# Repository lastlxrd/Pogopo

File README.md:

# Pogopo

*Both Pogopo and PogopoOS are still in the early stages of development.*

[@lastlxrd](https://github.com/lastlxrd) 2026

## Getting Started

Pogopo is still under active development. More complete documentation will be added as the hardware and software mature.

[Documentation](https://lastlxrd.github.io/Pogopo/)
[FAQ](https://lastlxrd.github.io/Pogopo/faq/)

## Project Summary

Pogopo is a custom hand-built handheld console based on the ESP32-S3. It combines a low-power monochrome display, physical controls, audio, motion sensing, removable storage, haptic feedback, and custom power management in one compact device.

The goal is to create a standalone handheld capable of running native applications, utilities, emulators, and custom games through a simple graphical interface. The current device is a working development prototype, with both its hardware and software continuing to evolve.

## Hardware

- ESP32-S3 with 16 MB flash and 8 MB PSRAM
- Sharp LS027B7DH01 400 × 240 Memory LCD
- BMI270 motion sensor
- MAX98357A I2S audio amplifier
- microSD card over 4-bit SDMMC
- TCA9555 GPIO and button expander
- D-pad, A, B, Menu, Start, and Power controls
- Vibration motor
- Rechargeable battery
- Onboard charging and power management
- Custom PCB and 3D-printed enclosure

## PogopoOS

PogopoOS is the custom operating system and application platform developed specifically for the Pogopo console.

- ESP-IDF-based firmware
- Graphical launcher and application framework
- Reusable display, input, audio, storage, and sensor drivers
- Native I2S audio and WAV playback
- Motion sensing and visualization tools
- microSD file access
- Persistent settings
- Power quick menu and clean LCD shutdown
- Haptic feedback
- Native Game Boy emulation
- Full-speed Game Boy CPU execution
- Approximately 30 FPS LCD presentation
- Four-shade ordered dithering
- Fixed-rate Game Boy audio
- ROM loading from microSD
- Experimental PDX and Lua game runtime

Game ROMs and third-party game files are not included in this repository.

## Development

Pogopo and PogopoOS are developed through small tested milestones. Commit messages contain short summaries of individual changes, while longer technical notes are stored in [`docs/history/`](docs/history/).

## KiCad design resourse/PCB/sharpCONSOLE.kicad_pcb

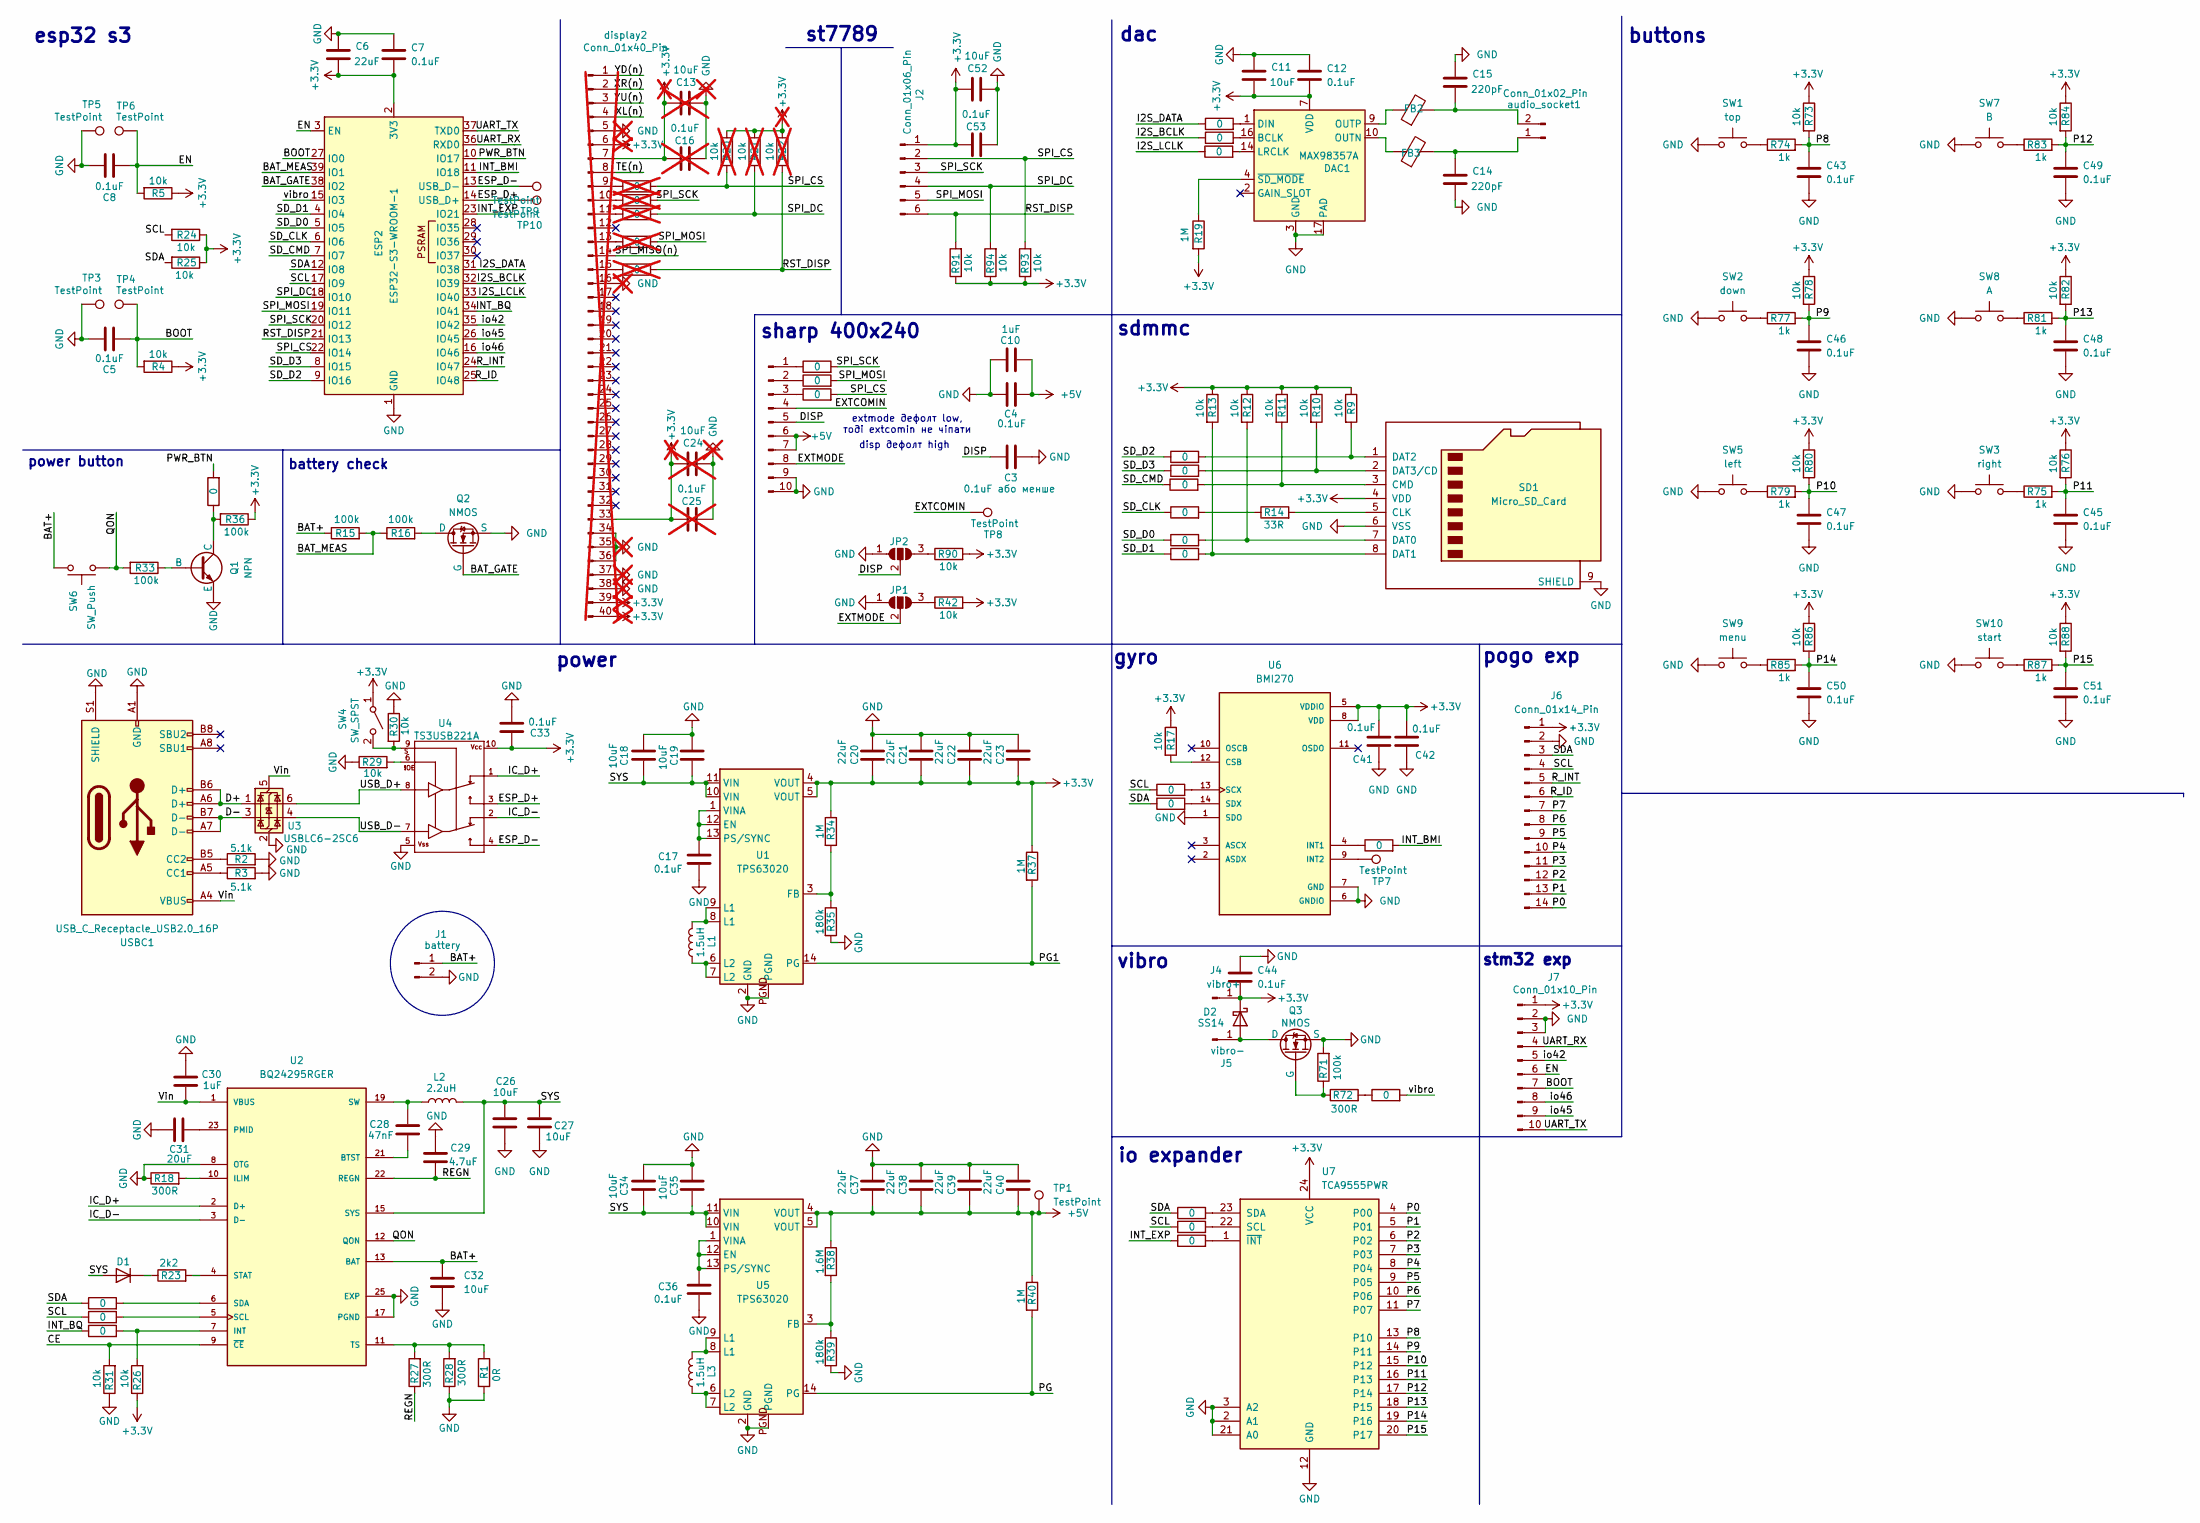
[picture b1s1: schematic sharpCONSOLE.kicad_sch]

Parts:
C3: 0.1uF або менше; C_0805_2012Metric
C4, C5, C7, C8, C12, C17, C33, C36, C41, C42, C43, C44, C45, C46, C47, C48, C49, C50, C51, C53: 0.1uF; C_0805_2012Metric
C6, C20, C21, C22, C23, C37, C38, C39, C40: 22uF; C_0805_2012Metric
C10, C30: 1uF; C_0805_2012Metric
C11, C18, C19, C26, C27, C32, C34, C35, C52: 10uF; C_0805_2012Metric
C13, C24: 10uF; C_0805_2012Metric; not fitted
C14, C15: 220pF; C_0805_2012Metric
C16, C25: 0.1uF; C_0805_2012Metric; not fitted
C28: 47nF; C_0805_2012Metric
C29: 4.7uF; C_0805_2012Metric
C31: 20uF; C_0805_2012Metric
D1: D; LED_0805_2012Metric
D2: SS14; D_SMA
DAC1: MAX98357A; TQFN-16-1EP_3x3mm_P0.5mm_EP1.23x1.23mm
ESP2: ESP32-S3-WROOM-1
FB2, FB3: 600; R_0805_2012Metric
J1: battery; PinHeader_1x02_P2.54mm_Vertical
J2: Conn_01x06_Pin; pad_6pin
J4: vibro+; TestPoint_Pad_1.5x1.5mm
J5: vibro-; TestPoint_Pad_1.5x1.5mm
J6: Conn_01x14_Pin; pads rp2040
J7: Conn_01x10_Pin; pad_10pin
J9: Conn_01x10_Pin; TE_1-1734839-0_1x10-1MP_P0.5mm_Horizontal
JP1, JP2: SolderJumper_3_Open; SolderJumper-3_P1.3mm_Open_RoundedPad1.0x1.5mm
L1, L3: 1.5uH; L_Chilisin_BMRA00050530
L2: 2.2uH; L_Chilisin_BMRA00050530
Q1: NPN; SOT-23-3
Q2, Q3: NMOS; SOT-23
R1: 0R; R_0805_2012Metric
R2, R3: 5.1k; R_0805_2012Metric
R4, R5, R9, R10, R11, R12, R13, R17, R24, R25, R26, R29, R30, R31, R42, R73, R76, R78, R80, R82, R84, R86, R88, R90, R91, R93, R94: 10k; R_0805_2012Metric
R14: 33R; R_0805_2012Metric
R15, R16, R33, R36, R71: 100k; R_0805_2012Metric
R18, R27, R28, R72: 300R; R_0805_2012Metric
R19, R34, R37, R40: 1M; R_0805_2012Metric
R20, R21, R22: 10k; R_0805_2012Metric; not fitted
R23: 2k2; R_0805_2012Metric
R35, R39: 180k; R_0805_2012Metric
R38: 1.6M; R_0805_2012Metric
R43, R44, R45, R46, R47, R48, R52, R53, R54, R55, R56, R57, R58, R59, R60, R61, R62, R63, R64, R70, R96, R97, R98: 0; R_0402_1005Metric
R65, R66, R67, R68, R69: 0; R_0402_1005Metric; not fitted
R74, R75, R77, R79, R81, R83, R85, R87: 1k; R_0805_2012Metric
SD1: Micro_SD_Card; microSD_HC_Hirose_DM3AT-SF-PEJM5
SW1: top; SW_Dome_10mm
SW2: down; SW_Dome_10mm
SW3: right; SW_Dome_10mm
SW4: SW_SPST; SW_DIP_SPSTx01_Slide_Copal_CVS-01xB_W5.9mm_P1mm
SW5: left; SW_Dome_10mm
SW6: SW_Push; SW_SPST_B3U-3000P
SW7: B; SW_Dome_10mm
SW8: A; SW_Dome_10mm
SW9: menu; SW_Dome_10mm
SW10: start; SW_Dome_10mm
TP1: TestPoint; TestPoint_Pad_1.5x1.5mm
TP3, TP4, TP5, TP6, TP9, TP10: TestPoint; TestPoint_Pad_D1.0mm
TP7, TP8: TestPoint; TestPoint_Pad_1.0x1.0mm
U1, U5: TPS63020
U2: BQ24295RGER; IC_BQ24295RGER; PARTREV B
U3: USBLC6-2SC6; SOT-23-6
U4: TS3USB221A; QFN-10-RSE
U6: BMI270; XDCR_BMI270
U7: TCA9555PWR; TSSOP-24_4.4x7.8mm_P0.65mm
USBC1: USB_C_Receptacle_USB2.0_16P; USB_C_Receptacle_GCT_USB4110
audio_socket1: Conn_01x02_Pin; PinHeader_1x02_P2.00mm_Vertical
display2: Conn_01x40_Pin; Hirose_FH12-40S-0.5SH_1x40-1MP_P0.50mm_Horizontal; not fitted

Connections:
+3.3V: C6.2, C7.2, C11.2, C12.2, C13.2, C16.2, C20.1, C21.1, C22.1, C23.1, C24.2, C25.2, C33.2, C41.2, C42.2, C44.2, C52.2, C53.2, D2.1 (K), DAC1.7 (VDD), DAC1.8 (VDD), ESP2.2 (3V3), J2.1, J4.1, J6.1, J7.1, R4.1, R5.1, R9.1, R10.1, R11.1, R12.1, R13.1, R17.1, R19.2, R20.1, R21.1, R22.1, R24.1, R25.1, R26.1, R34.1, R36.1, R37.1, R42.2, R73.1, R76.1, R78.1, R80.1, R82.1, R84.1, R86.1, R88.1, R90.2, R91.1, R93.1, R94.1, SD1.4 (VDD), SW4.1 (A), U1.4 (VOUT), U1.5 (VOUT), U4.10, U6.5 (VDDIO), U6.8 (VDD), U7.24 (VCC), display2.6, display2.7, display2.33, display2.39, display2.40
+5V: C4.2, C10.2, C37.1, C38.1, C39.1, C40.1, J9.6, J9.7, R38.1, R40.1, TP1.1, U5.4 (VOUT), U5.5 (VOUT)
/BAT+: C32.1, J1.1, R15.1, SW6.2, U2.13 (BAT), U2.14 (BAT)
/BAT_GATE: ESP2.38 (IO2), Q2.2 (G)
/BAT_MEAS: ESP2.39 (IO1), R15.2, R16.1
/BOOT: C5.1, ESP2.27 (IO0), J7.7, R4.2, TP4.1
/CE: R31.2, U2.9 (~CE)
/D+: U3.1 (I/O1), USBC1.A6 (D+), USBC1.B6 (D+)
/D-: U3.3 (I/O2), USBC1.A7 (D-), USBC1.B7 (D-)
/DISP: C3.1, J9.5, JP2.2 (C)
/EN: C8.1, ESP2.3 (EN), J7.6, R5.2, TP6.1
/ESP_D+: ESP2.14 (USB_D+), TP10.1, U4.3
/ESP_D-: ESP2.13 (USB_D-), TP9.1, U4.4
/EXTCOMIN: J9.4, TP8.1
/EXTMODE: J9.8, JP1.2 (C)
/I2S_BCLK: ESP2.32 (IO39), R62.1
/I2S_DATA: ESP2.31 (IO38), R61.1
/I2S_LCLK: ESP2.33 (IO40), R63.1
/IC_D+: U2.2 (D+), U4.1
/IC_D-: U2.3 (D-), U4.2
/INT_BMI: ESP2.11 (IO18), R55.2
/INT_BQ: ESP2.34 (IO41), R60.1
/INT_EXP: ESP2.23 (IO21), R54.1
/P0: J6.14, U7.4 (P00)
/P1: J6.13, U7.5 (P01)
/P2: J6.12, U7.6 (P02)
/P3: J6.11, U7.7 (P03)
/P4: J6.10, U7.8 (P04)
/P5: J6.9, U7.9 (P05)
/P6: J6.8, U7.10 (P06)
/P7: J6.7, U7.11 (P07)
/P8: C43.1, R73.2, R74.2, U7.13 (P10)
/P9: C46.1, R77.2, R78.2, U7.14 (P11)
/P10: C47.1, R79.2, R80.2, U7.15 (P12)
/P11: C45.1, R75.2, R76.2, U7.16 (P13)
/P12: C49.1, R83.2, R84.2, U7.17 (P14)
/P13: C48.1, R81.2, R82.2, U7.18 (P15)
/P14: C50.1, R85.2, R86.2, U7.19 (P16)
/P15: C51.1, R87.2, R88.2, U7.20 (P17)
/PG: R40.2, U5.14 (PG)
/PG1: R37.2, U1.14 (PG)
/PWR_BTN: ESP2.10 (IO17), R64.2
/QON: R33.2, SW6.1, U2.12 (QON)
/REGN: C29.1, R27.1, U2.22 (REGN)
/RST_DISP: ESP2.21 (IO13), J2.6, R22.2, R69.2, R91.2
/R_ID: ESP2.25 (IO48), J6.6
/R_INT: ESP2.24 (IO47), J6.5
/SCL: ESP2.17 (IO9), J6.4, R24.2, R53.1, R56.1, R59.1
/SDA: ESP2.12 (IO8), J6.3, R25.2, R52.1, R57.1, R58.1
/SD_CLK: ESP2.6 (IO6), R46.1
/SD_CMD: ESP2.7 (IO7), R45.1
/SD_D0: ESP2.5 (IO5), R47.1
/SD_D1: ESP2.4 (IO4), R48.1
/SD_D2: ESP2.9 (IO16), R43.1
/SD_D3: ESP2.8 (IO15), R44.1
/SPI_CS: ESP2.22 (IO14), J2.2, R20.2, R68.2, R93.2, R98.2
/SPI_DC: ESP2.18 (IO10), J2.4, R21.2, R66.2, R94.2
/SPI_MOSI: ESP2.19 (IO11), J2.5, R67.2, R97.2
/SPI_SCK: ESP2.20 (IO12), J2.3, R65.2, R96.2
/SYS: C18.2, C19.2, C26.1, C27.1, C34.2, C35.2, D1.2 (A), L2.2, U1.10 (VIN), U1.11 (VIN), U2.15 (SYS), U2.16 (SYS), U5.10 (VIN), U5.11 (VIN)
/UART_RX: ESP2.36 (RXD0), J7.4
/UART_TX: ESP2.37 (TXD0), J7.10
/USB_D+: U3.6 (I/O1), U4.8
/USB_D-: U3.4 (I/O2), U4.7
/io42: ESP2.35 (IO42), J7.5
/io45: ESP2.26 (IO45), J7.9
/io46: ESP2.16 (IO46), J7.8
/vibro: ESP2.15 (IO3), R70.2
GND: C3.2, C4.1, C5.2, C6.1, C7.1, C8.2, C10.1, C11.1, C12.1, C13.1, C14.2, C15.1, C16.1, C17.2, C18.1, C19.1, C20.2, C21.2, C22.2, C23.2, C24.1, C25.1, C26.2, C27.2, C29.2, C30.1, C31.1, C32.2, C33.1, C34.1, C35.1, C36.2, C37.2, C38.2, C39.2, C40.2, C41.1, C42.1, C43.2, C44.1, C45.2, C46.2, C47.2, C48.2, C49.2, C50.2, C51.2, C52.1, C53.1, DAC1.3 (GND), DAC1.11 (GND), DAC1.15 (GND), DAC1.17 (PAD), ESP2.1 (GND), ESP2.40 (GND), ESP2.41 (GND), J1.2, J6.2, J7.2, J7.3, J9.9, J9.10, JP1.1 (A), JP2.1 (A), Q1.3 (E), Q2.3 (S), Q3.3 (S), R1.2, R2.2, R3.2, R18.1, R28.1, R29.1, R30.1, R31.1, R35.2, R39.2, R71.2, SD1.6 (VSS), SD1.9 (SHIELD), SW1.1, SW2.1, SW3.1, SW5.1, SW7.1, SW8.1, SW9.1, SW10.1, TP3.1, TP5.1, U1.2 (GND), U1.PGND, U2.8 (OTG), U2.17 (PGND), U2.18 (PGND), U2.25 (EXP), U3.2 (GND), U4.5, U5.2 (GND), U5.PGND, U6.1 (SDO), U6.6 (GNDIO), U6.7 (GND), U7.2 (A1), U7.3 (A2), U7.12 (GND), U7.21 (A0), USBC1.A1 (GND), USBC1.A12 (GND), USBC1.B1 (GND), USBC1.B12 (GND), USBC1.S1 (SHIELD), display2.5, display2.16, display2.34, display2.35, display2.36, display2.37, display2.38
unnamed: C28.2, L2.1, U2.19 (SW), U2.20 (SW)
unnamed: D1.1 (K), R23.1
unnamed: D2.2 (A), J5.1, Q3.1 (D)
unnamed: DAC1.16 (BCLK), R62.2
unnamed: DAC1.1 (DIN), R61.2
unnamed: DAC1.14 (LRCLK), R63.2
unnamed: DAC1.10 (OUTN), FB3.1
unnamed: DAC1.9 (OUTP), FB2.1
unnamed: DAC1.4 (~SD_MODE), R19.1
unnamed: J9.1, R96.1
unnamed: J9.2, R97.1
unnamed: J9.3, R98.1
unnamed: JP1.3 (B), R42.1
unnamed: JP2.3 (B), R90.1
unnamed: L1.1, U1.6 (L2), U1.7 (L2)
unnamed: L1.2, U1.8 (L1), U1.9 (L1)
unnamed: L3.1, U5.6 (L2), U5.7 (L2)
unnamed: L3.2, U5.8 (L1), U5.9 (L1)
unnamed: Q1.2 (B), R33.1
unnamed: Q1.1 (C), R36.2, R64.1
unnamed: Q2.1 (D), R16.2
unnamed: Q3.2 (G), R71.1, R72.1
unnamed: R14.1, R46.2
unnamed: R29.2, U4.6
unnamed: R65.1, display2.10
unnamed: R66.1, display2.11
unnamed: R67.1, display2.13
unnamed: R68.1, display2.9
unnamed: R69.1, display2.15
unnamed: R70.1, R72.2
unnamed: R74.1, SW1.2
unnamed: R75.1, SW3.2
unnamed: R77.1, SW2.2
unnamed: R79.1, SW5.2
unnamed: R81.1, SW8.2
unnamed: R83.1, SW7.2
unnamed: R85.1, SW9.2
unnamed: R87.1, SW10.2
unnamed: R14.2, SD1.5 (CLK)
unnamed: R11.2, R45.2, SD1.3 (CMD)
unnamed: R12.2, R47.2, SD1.7 (DAT0)
unnamed: R13.2, R48.2, SD1.8 (DAT1)
unnamed: R9.2, R43.2, SD1.1 (DAT2)
unnamed: R10.2, R44.2, SD1.2 (DAT3/CD)
unnamed: R30.2, SW4.2 (B), U4.9
unnamed: C17.1, U1.1 (VINA), U1.12 (EN), U1.13 (PS/SYNC)
unnamed: R34.2, R35.1, U1.3 (FB)
unnamed: C28.1, U2.21 (BTST)
unnamed: R18.2, U2.10 (ILIM)
unnamed: R26.2, R60.2, U2.7 (INT)
unnamed: C31.2, U2.23 (PMID)
unnamed: R59.2, U2.5 (SCL)
unnamed: R58.2, U2.6 (SDA)
unnamed: R23.2, U2.4 (STAT)
unnamed: R1.1, R27.2, R28.2, U2.11 (TS)
unnamed: C36.1, U5.1 (VINA), U5.12 (EN), U5.13 (PS/SYNC)
unnamed: R38.2, R39.1, U5.3 (FB)
unnamed: R17.2, U6.12 (CSB)
unnamed: R55.1, U6.4 (INT1)
unnamed: TP7.1, U6.9 (INT2)
unnamed: R56.2, U6.13 (SCX)
unnamed: R57.2, U6.14 (SDX)
unnamed: R53.2, U7.22 (SCL)
unnamed: R52.2, U7.23 (SDA)
unnamed: R54.2, U7.1 (~INT)
unnamed: R3.1, USBC1.A5 (CC1)
unnamed: R2.1, USBC1.B5 (CC2)
unnamed: C14.1, FB3.2, audio_socket1.1
unnamed: C15.2, FB2.2, audio_socket1.2
VBUS: C30.2, U2.1 (VBUS), U2.24 (VBUS), U3.5 (VBUS), USBC1.A4 (VBUS), USBC1.A9 (VBUS), USBC1.B4 (VBUS), USBC1.B9 (VBUS)

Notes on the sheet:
stm32 exp
esp32 s3
power button
sdmmc
dac
power
buttons
io expander
st7789
gyro
disp дефолт high
pogo exp
battery check
sharp 400x240
vibro
extmode дефолт low, тоді extcomin не чіпати

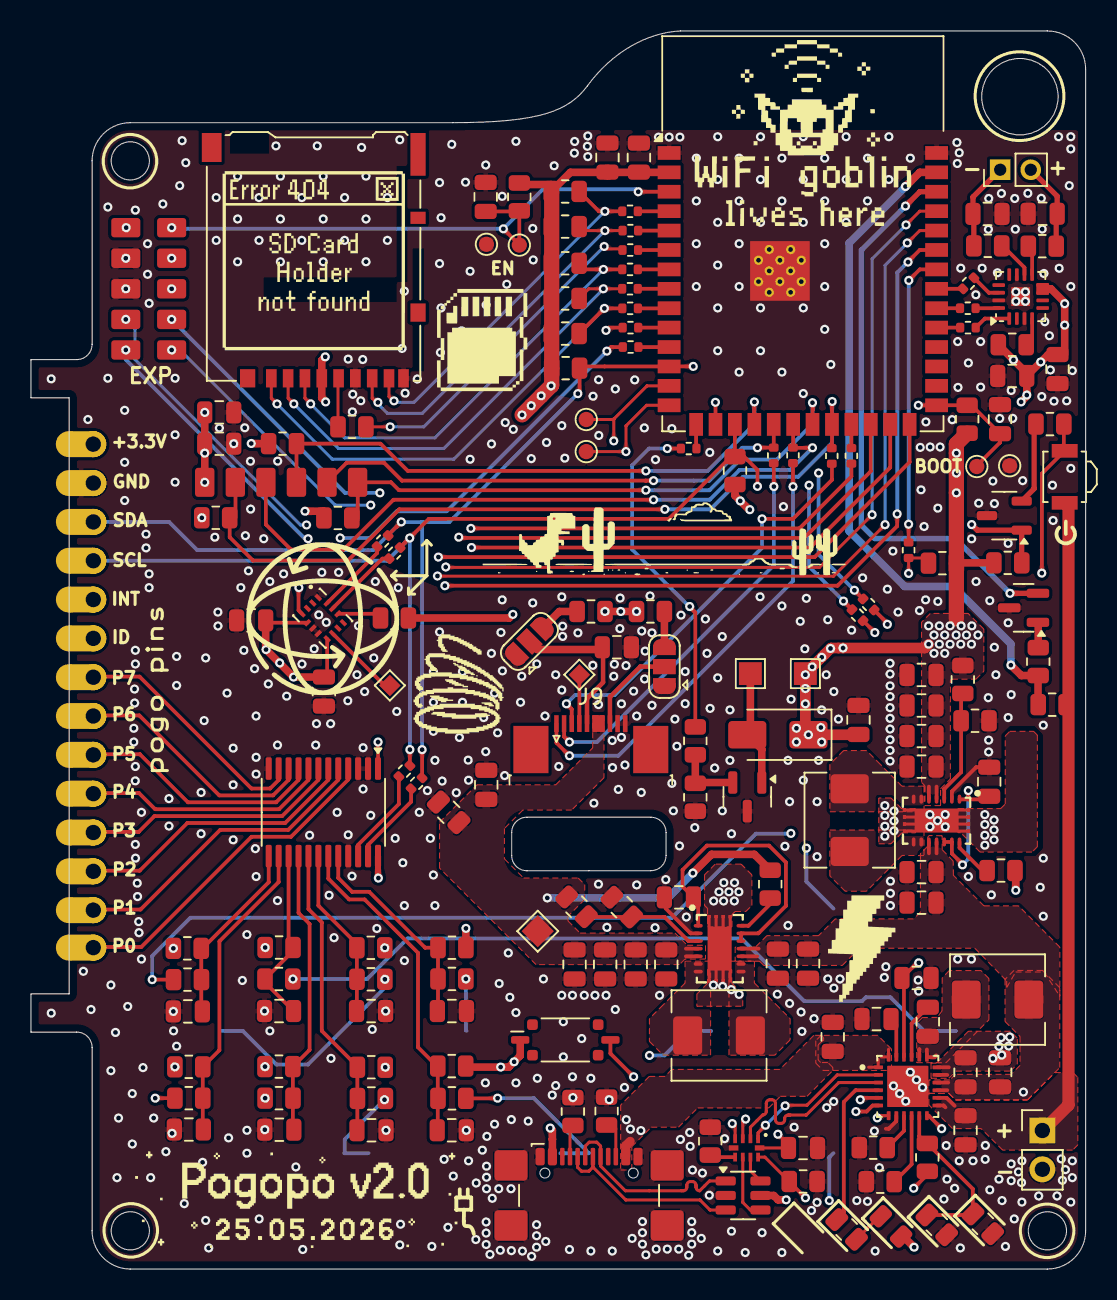
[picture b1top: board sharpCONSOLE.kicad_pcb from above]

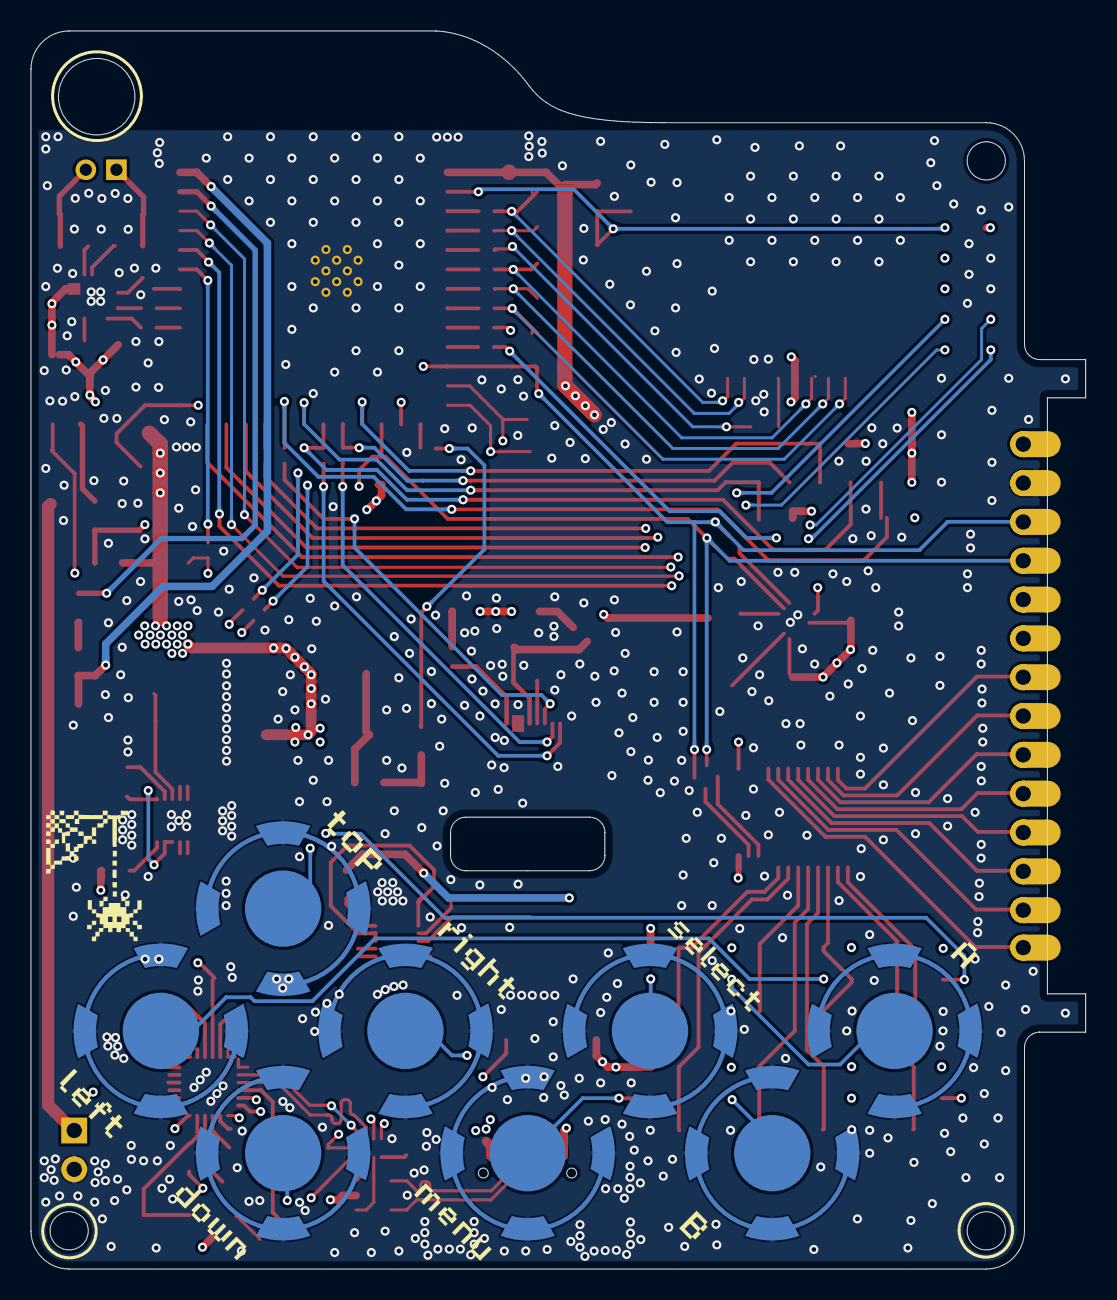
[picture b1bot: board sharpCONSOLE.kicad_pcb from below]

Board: 4 copper layers, 69.0 x 81.0 mm, 175 parts (8 on the bottom side), 134 nets.

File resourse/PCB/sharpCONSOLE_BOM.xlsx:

№ | Тип | Номінал / Part | Корпус / Footprint | К-сть | Позначення на платі | Примітка | Datasheet
1 | Розʼєм / джампер | Conn_01x02_Pin | PinHeader_1x02_P2.00mm_Vertical | 1 | audio_socket1
2 | Конденсатор | 0.1uF або менше | 0805 / 2012 metric | 1 | C3
3 | Конденсатор | 0.1uF | 0805 / 2012 metric | 20 | C4,C5,C7,C8,C12,C17,C33,C36,C41,C42,C43,C44,C45,C46,C47,C48,C49,C50,C51,C53
4 | Конденсатор | 22uF | 0805 / 2012 metric | 9 | C6,C20,C21,C22,C23,C37,C38,C39,C40
5 | Конденсатор | 1uF | 0805 / 2012 metric | 2 | C10,C30
6 | Конденсатор | 10uF | 0805 / 2012 metric | 9 | C11,C18,C19,C26,C27,C32,C34,C35,C52
8 | Конденсатор | 220pF | 0805 / 2012 metric | 2 | C14,C15
10 | Конденсатор | 47nF | 0805 / 2012 metric | 1 | C28
11 | Конденсатор | 4.7uF | 0805 / 2012 metric | 1 | C29
12 | Конденсатор | 20uF | 0805 / 2012 metric | 1 | C31
13 | LED / діод | D | LED 0805 / 2012 | 1 | D1
14 | Діод | SS14 | SMA diode package | 1 | D2 |  | https://www.vishay.com/docs/88746/ss12.pdf
15 | Діод | MAX98357A | TQFN-16-1EP_3x3mm_P0.5mm_EP1.23x1.23mm | 1 | DAC1 |  | https://www.analog.com/media/en/technical-documentation/data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
17 | Мікросхема / модуль | ESP32-S3-WROOM-1 | ESP32-S3-WROOM-1 | 1 | ESP2 |  | https://www.espressif.com/sites/default/files/documentation/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
18 | Ferrite bead | 600 | 0805 / 2012 metric | 2 | FB2,FB3
19 | Розʼєм / джампер | battery | PinHeader_1x02_P2.54mm_Vertical | 1 | J1
20 | Розʼєм / джампер | Conn_01x06_Pin | pad_6pin | 1 | J2
21 | Розʼєм / джампер | vibro+ | TestPoint_Pad_1.5x1.5mm | 1 | J4
22 | Розʼєм / джампер | vibro- | TestPoint_Pad_1.5x1.5mm | 1 | J5
23 | Розʼєм / джампер | Conn_01x14_Pin | pads rp2040 | 1 | J6
24 | Розʼєм / джампер | Conn_01x10_Pin | pad_10pin | 1 | J7
25 | Розʼєм / джампер | Conn_01x10_Pin | TE_1-1734839-0_1x10-1MP_P0.5mm_Horizontal | 1 | J9
26 | Розʼєм / джампер | SolderJumper_3_Open | SolderJumper-3_P1.3mm_Open_RoundedPad1.0x1.5mm | 2 | JP1,JP2
27 | Індуктивність | 1.5uH | L_Chilisin_BMRA00050530 | 2 | L1,L3
28 | Індуктивність | 2.2uH | L_Chilisin_BMRA00050530 | 1 | L2
29 | Транзистор / MOSFET | NPN | SOT-23-3 | 1 | Q1 |  | https://ngspice.sourceforge.io/docs/ngspice-html-manual/manu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
30 | Транзистор / MOSFET | NMOS | SOT-23 | 2 | Q2,Q3 |  | https://ngspice.sourceforge.io/docs/ngspice-html-manual/manu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
31 | Резистор | 0R | 0805 / 2012 metric | 1 | R1
32 | Резистор | 5.1k | 0805 / 2012 metric | 2 | R2,R3
33 | Резистор | 10k | 0805 / 2012 metric | 27 | R4,R5,R9,R10,R11,R12,R13,R17,R24,R25,R26,R29,R30,R31,R42,R73,R76,R78,R80,R82,R8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
34 | Резистор | 33R | 0805 / 2012 metric | 1 | R14
35 | Резистор | 100k | 0805 / 2012 metric | 5 | R15,R16,R33,R36,R71
36 | Резистор | 300R | 0805 / 2012 metric | 4 | R18,R27,R28,R72
37 | Резистор | 1M | 0805 / 2012 metric | 4 | R19,R34,R37,R40
39 | Резистор | 2k2 | 0805 / 2012 metric | 1 | R23
40 | Резистор | 180k | 0805 / 2012 metric | 2 | R35,R39
41 | Резистор | 1.6M | 0805 / 2012 metric | 1 | R38
42 | Резистор | 0 | 0402 / 1005 metric | 23 | R43,R44,R45,R46,R47,R48,R52,R53,R54,R55,R56,R57,R58,R59,R60,R61,R62,R63,R64,R70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
44 | Резистор | 1k | 0805 / 2012 metric | 8 | R74,R75,R77,R79,R81,R83,R85,R87
45 | Розʼєм / джампер | Micro_SD_Card | microSD_HC_Hirose_DM3AT-SF-PEJM5 | 1 | SD1 |  | https://www.we-online.com/components/products/datasheet/6930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
46 | Кнопка / перемикач | top | SW_Dome_10mm | 1 | SW1
47 | Кнопка / перемикач | down | SW_Dome_10mm | 1 | SW2
48 | Кнопка / перемикач | right | SW_Dome_10mm | 1 | SW3
49 | Кнопка / перемикач | SW_SPST | SW_DIP_SPSTx01_Slide_Copal_CVS-01xB_W5.9mm_P1mm | 1 | SW4
50 | Кнопка / перемикач | left | SW_Dome_10mm | 1 | SW5
51 | Кнопка / перемикач | SW_Push | SW_SPST_B3U-3000P | 1 | SW6
52 | Кнопка / перемикач | B | SW_Dome_10mm | 1 | SW7
53 | Кнопка / перемикач | A | SW_Dome_10mm | 1 | SW8
54 | Кнопка / перемикач | menu | SW_Dome_10mm | 1 | SW9
55 | Кнопка / перемикач | start | SW_Dome_10mm | 1 | SW10
56 | Test point | TestPoint | TestPoint_Pad_1.5x1.5mm | 1 | TP1
57 | Test point | TestPoint | TestPoint_Pad_D1.0mm | 6 | TP3,TP4,TP5,TP6,TP9,TP10
58 | Test point | TestPoint | TestPoint_Pad_1.0x1.0mm | 2 | TP7,TP8
59 | Мікросхема / модуль | TPS63020 | TPS63020 | 2 | U1,U5 |  | http://www.ti.com/lit/ds/symlink/tps63000.pdf
60 | Мікросхема / модуль | BQ24295RGER | IC_BQ24295RGER | 1 | U2
61 | Мікросхема / модуль | USBLC6-2SC6 | SOT-23-6 | 1 | U3 |  | https://www.st.com/resource/en/datasheet/usblc6-2.pdf
62 | Мікросхема / модуль | TS3USB221A | QFN-10-RSE | 1 | U4
63 | Мікросхема / модуль | BMI270 | XDCR_BMI270 | 1 | U6
64 | Мікросхема / модуль | TCA9555PWR | TSSOP-24_4.4x7.8mm_P0.65mm | 1 | U7 |  | http://www.ti.com/lit/ds/symlink/tca9555.pdf
65 | Мікросхема / модуль | USB_C_Receptacle_USB2.0_16P | USB_C_Receptacle_GCT_USB4110 | 1 | USBC1 |  | https://www.usb.org/sites/default/files/documents/usb_type-c.zip

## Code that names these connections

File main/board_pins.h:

#pragma once
namespace board {
constexpr int I2C_SDA = 8;
constexpr int I2C_SCL = 9;
constexpr int IMU_INT = 18;
constexpr int TCA9555_INT = 21;
constexpr int LCD_SCK = 12;
constexpr int LCD_MOSI = 11;
constexpr int LCD_CS = 14;
constexpr int AUDIO_DOUT = 38;
constexpr int AUDIO_BCLK = 39;
constexpr int AUDIO_LRCK = 40;
constexpr int SD_D0 = 5;
constexpr int SD_D1 = 4;
constexpr int SD_D2 = 16;
constexpr int SD_D3 = 15;
constexpr int SD_CLK = 6;
constexpr int SD_CMD = 7;
constexpr int VIBRO = 3;
constexpr int RGB_LED = 48;
constexpr int POWER_BUTTON = 17;
constexpr int CHARGER_INT = 41;
constexpr int BAT_MEAS = 1;
constexpr int BAT_GATE = 2;
}
